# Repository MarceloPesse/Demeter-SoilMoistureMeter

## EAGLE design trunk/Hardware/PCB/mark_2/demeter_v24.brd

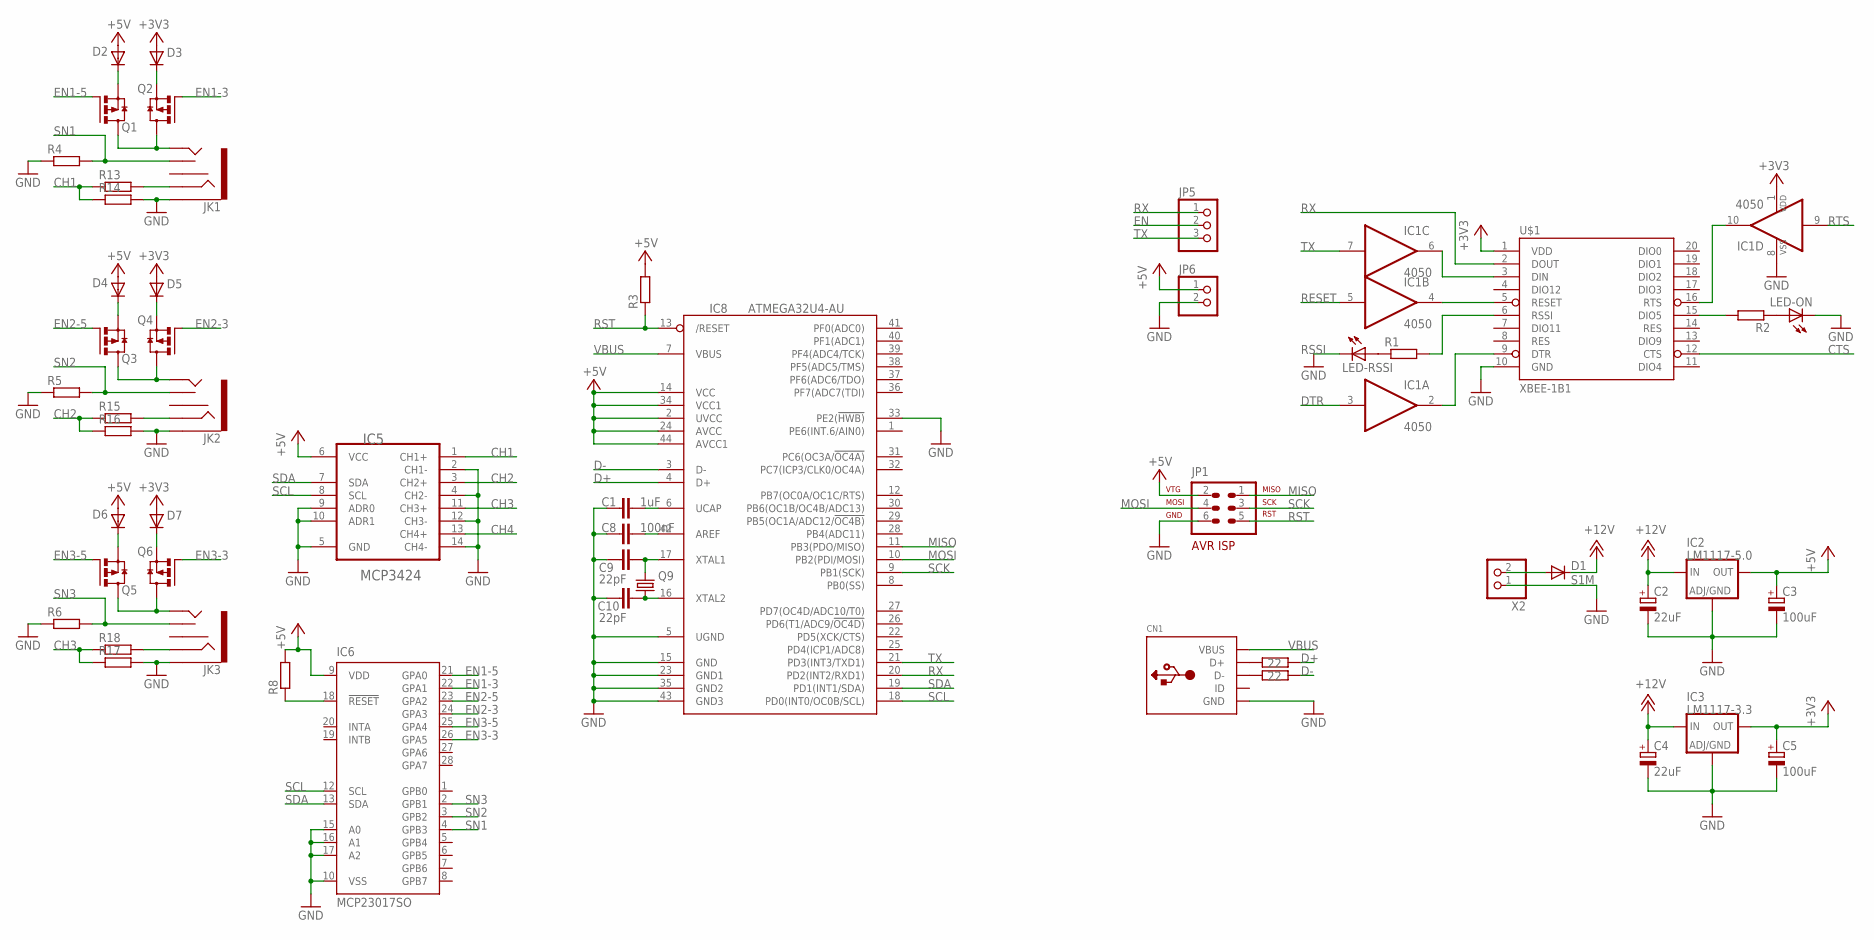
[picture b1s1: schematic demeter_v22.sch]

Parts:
C1: 1uF; C0805K
C2, C4: 22uF; PANASONIC_D
C3, C5: 100uF; PANASONIC_D
C8: 100nF; C0805K
C9, C10: 22pF; C0805K
CN1: USBMINIB; USB-MINIB
D1: S1M; DO-214AC
D2, D3, D4, D5, D6, D7: MBR0520; SOD123
IC1: 4050; SO16
IC2: LM1117-5.0; DPACK
IC3: LM1117-3.3; DPACK
IC5: MCP3424; SO14
IC6: MCP23017SO; SO28W
IC8: ATMEGA32U4-AU; TQFP44
JK1, JK2, JK3: AUDIO-JACK2PTH; AUDIO-JACK
JP1: AVR-ISP-6
JP5: PINHD-1X3180; 1X03
JP6: PINHD-1X2; 1X02
LED-ON: LED0805; CHIP-LED0805
LED-RSSI: LED0805; CHIP-LED0805
Q1, Q2, Q3, Q4, Q5, Q6: IRLML6402; SOT23
Q9: CRYSTALHC49UP; HC49UP
R1, R2, R3, R4, R5, R6, R8, R13, R14, R15, R16, R17, R18: R-EU_R0805; R0805
R9, R10: 22; R0805
U$1: XBEE-1B1; XBEE-1
X2: W237-102

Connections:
+3V3: C5.+, D3.A, D5.A, D7.A, IC1.1 (VDD), IC3.4 (OUT), U$1.1 (VDD); also elsewhere on the board
+5V: C3.+, D2.A, D4.A, D6.A, IC2.4 (OUT), IC5.6 (VCC), IC6.9 (VDD), IC8.2 (UVCC), IC8.14 (VCC), IC8.24 (AVCC), IC8.34 (VCC1), IC8.44 (AVCC1), JP1.2 (VTG), JP6.1, R3.2, R8.2; also elsewhere on the board
+12V: C2.+, C4.+, D1.C, IC2.3 (IN), IC3.3 (IN)
CH1: IC5.1 (CH1+), R13.1, R14.1
CH2: IC5.3 (CH2+), R15.1, R16.1
CH3: IC5.11 (CH3+), R17.1, R18.1
CTS: U$1.12 (CTS); also elsewhere on the board
D+: IC8.4 (D+), R9.1
D-: IC8.3 (D-), R10.1
DTR: IC1.3 (I); also elsewhere on the board
EN: JP5.2; also elsewhere on the board
EN1-3: IC6.22 (GPA1), Q2.1 (G)
EN1-5: IC6.21 (GPA0), Q1.1 (G)
EN2-3: IC6.24 (GPA3), Q4.1 (G)
EN2-5: IC6.23 (GPA2), Q3.1 (G)
EN3-3: IC6.26 (GPA5), Q6.1 (G)
EN3-5: IC6.25 (GPA4), Q5.1 (G)
MISO: IC8.11 (PB3(PDO/MISO)), JP1.1 (MISO)
MOSI: IC8.10 (PB2(PDI/MOSI)), JP1.4 (MOSI)
unnamed: IC1.6 (O), U$1.3 (DIN)
unnamed: IC1.4 (O), U$1.5 (RESET)
unnamed 24: LED-RSSI.A, R1.1; also elsewhere on the board
unnamed: IC1.2 (O), U$1.9 (DTR)
unnamed: IC1.10 (O), U$1.16 (RTS)
unnamed: IC6.18 (!RESET), R8.1
unnamed: JK1.TIP, Q1.3 (D), Q2.3 (D)
unnamed: D2.C, Q1.2 (S)
unnamed: D3.C, Q2.2 (S)
unnamed: JK2.TIP, Q3.3 (D), Q4.3 (D)
unnamed: D4.C, Q3.2 (S)
unnamed: D5.C, Q4.2 (S)
unnamed: JK3.TIP, Q5.3 (D), Q6.3 (D)
unnamed: D6.C, Q5.2 (S)
unnamed: D7.C, Q6.2 (S)
unnamed: C1.1, IC8.6 (UCAP)
unnamed: C8.1, IC8.42 (AREF)
unnamed: C9.1, IC8.17 (XTAL1), Q9.2
unnamed: C10.1, IC8.16 (XTAL2), Q9.1
unnamed: CN1.D+, R9.2
unnamed: CN1.D-, R10.2
unnamed: JK1.RING, R13.2
unnamed: JK2.RING, R15.2
unnamed: JK3.RING, R18.2
unnamed: LED-ON.A, R2.1
unnamed: R2.2, U$1.15 (DIO5)
RESET: IC1.5 (I); also elsewhere on the board
RSSI: R1.2, U$1.6 (RSSI)
RST: IC8.13 (/RESET), JP1.5 (RST), R3.1
RTS: IC1.9 (I); also elsewhere on the board
RX: IC8.20 (PD2(INT2/RXD1)), JP5.1, U$1.2 (DOUT); also elsewhere on the board
SCK: IC8.9 (PB1(SCK)), JP1.3 (SCK)
SCL: IC5.8 (SCL), IC6.12 (SCL), IC8.18 (PD0(INT0/OC0B/SCL))
SDA: IC5.7 (SDA), IC6.13 (SDA), IC8.19 (PD1(INT1/SDA))
TX: IC1.7 (I), IC8.21 (PD3(INT3/TXD1)), JP5.3; also elsewhere on the board
VBUS: CN1.VBUS, IC8.7 (VBUS)

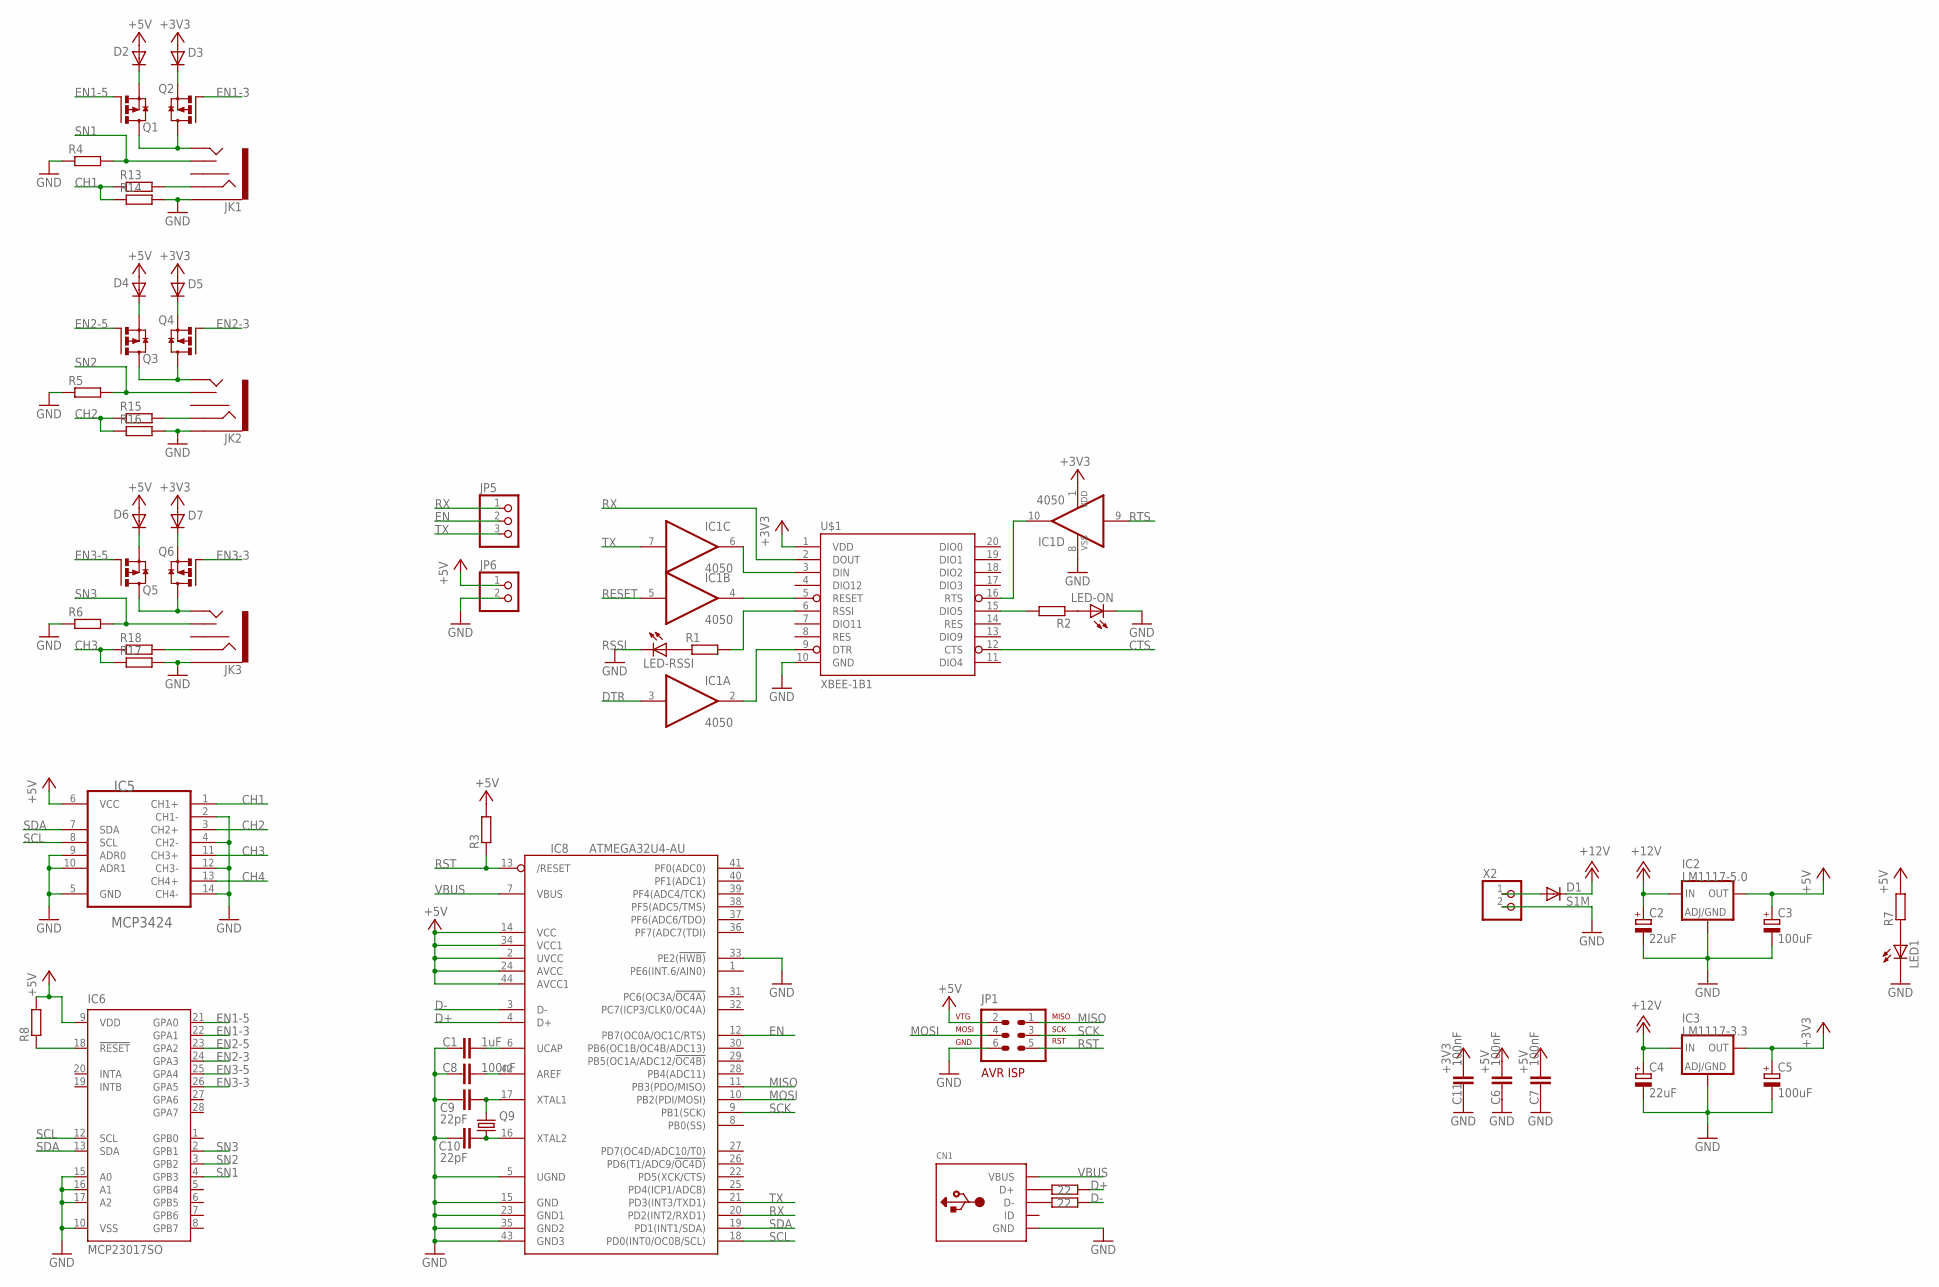
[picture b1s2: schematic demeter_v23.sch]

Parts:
C1: 1uF; C0805K
C2, C4: 22uF; PANASONIC_D
C3, C5: 100uF; PANASONIC_D
C6, C7, C8, C11: 100nF; C0805K
C9, C10: 22pF; C0805K
CN1: USBMINIB; USB-MINIB
D1: S1M; DO-214AC
D2, D3, D4, D5, D6, D7: MBR0520; SOD123
IC1: 4050; SO16
IC2: LM1117-5.0; DPACK
IC3: LM1117-3.3; DPACK
IC5: MCP3424; SO14
IC6: MCP23017SO; SO28W
IC8: ATMEGA32U4-AU; TQFP44
JK1, JK2, JK3: AUDIO-JACK2PTH; AUDIO-JACK
JP1: AVR-ISP-6
JP5: PINHD-1X3180; 1X03
JP6: PINHD-1X2; 1X02
LED1: LED0805; CHIP-LED0805
LED-ON: LED0805; CHIP-LED0805
LED-RSSI: LED0805; CHIP-LED0805
Q1, Q2, Q3, Q4, Q5, Q6: IRLML6402; SOT23
Q9: CRYSTALHC49UP; HC49UP
R1, R2, R3, R4, R5, R6, R7, R8, R13, R14, R15, R16, R17, R18: R-EU_R0805; R0805
R9, R10: 22; R0805
U$1: XBEE-1B1; XBEE-1
X2: W237-102

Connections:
+3V3: C5.+, C11.1, D3.A, D5.A, D7.A, IC1.1 (VDD), IC3.4 (OUT), U$1.1 (VDD); also elsewhere on the board
+5V: C3.+, C6.1, C7.1, D2.A, D4.A, D6.A, IC2.4 (OUT), IC5.6 (VCC), IC6.9 (VDD), IC8.2 (UVCC), IC8.14 (VCC), IC8.24 (AVCC), IC8.34 (VCC1), IC8.44 (AVCC1), JP1.2 (VTG), JP6.1, R3.2, R7.2, R8.2; also elsewhere on the board
+12V: C2.+, C4.+, D1.C, IC2.3 (IN), IC3.3 (IN)
CH1: IC5.1 (CH1+), R13.1, R14.1
CH2: IC5.3 (CH2+), R15.1, R16.1
CH3: IC5.11 (CH3+), R17.1, R18.1
CTS: U$1.12 (CTS); also elsewhere on the board
D+: IC8.4 (D+), R9.1
D-: IC8.3 (D-), R10.1
DTR: IC1.3 (I); also elsewhere on the board
EN: IC8.12 (PB7(OC0A/OC1C/RTS)), JP5.2
EN1-3: IC6.22 (GPA1), Q2.1 (G)
EN1-5: IC6.21 (GPA0), Q1.1 (G)
EN2-3: IC6.24 (GPA3), Q4.1 (G)
EN2-5: IC6.23 (GPA2), Q3.1 (G)
EN3-3: IC6.26 (GPA5), Q6.1 (G)
EN3-5: IC6.25 (GPA4), Q5.1 (G)
MISO: IC8.11 (PB3(PDO/MISO)), JP1.1 (MISO)
MOSI: IC8.10 (PB2(PDI/MOSI)), JP1.4 (MOSI)
unnamed 20: LED1.A, R7.1; also elsewhere on the board
unnamed: IC1.6 (O), U$1.3 (DIN)
unnamed: IC1.4 (O), U$1.5 (RESET)
unnamed 24: LED-RSSI.A, R1.1; also elsewhere on the board
unnamed: IC1.2 (O), U$1.9 (DTR)
unnamed: IC1.10 (O), U$1.16 (RTS)
unnamed: IC6.18 (!RESET), R8.1
unnamed: JK1.TIP, Q1.3 (D), Q2.3 (D)
unnamed: D2.C, Q1.2 (S)
unnamed: D3.C, Q2.2 (S)
unnamed: JK2.TIP, Q3.3 (D), Q4.3 (D)
unnamed: D4.C, Q3.2 (S)
unnamed: D5.C, Q4.2 (S)
unnamed: JK3.TIP, Q5.3 (D), Q6.3 (D)
unnamed: D6.C, Q5.2 (S)
unnamed: D7.C, Q6.2 (S)
unnamed: C1.1, IC8.6 (UCAP)
unnamed: C8.1, IC8.42 (AREF)
unnamed: C9.1, IC8.17 (XTAL1), Q9.2
unnamed: C10.1, IC8.16 (XTAL2), Q9.1
unnamed: CN1.D+, R9.2
unnamed: CN1.D-, R10.2
unnamed: JK1.RING, R13.2
unnamed: JK2.RING, R15.2
unnamed: JK3.RING, R18.2
unnamed: LED-ON.A, R2.1
unnamed: R2.2, U$1.15 (DIO5)
RESET: IC1.5 (I); also elsewhere on the board
RSSI: R1.2, U$1.6 (RSSI)
RST: IC8.13 (/RESET), JP1.5 (RST), R3.1
RTS: IC1.9 (I); also elsewhere on the board
RX: IC8.20 (PD2(INT2/RXD1)), JP5.1, U$1.2 (DOUT); also elsewhere on the board
SCK: IC8.9 (PB1(SCK)), JP1.3 (SCK)
SCL: IC5.8 (SCL), IC6.12 (SCL), IC8.18 (PD0(INT0/OC0B/SCL))
SDA: IC5.7 (SDA), IC6.13 (SDA), IC8.19 (PD1(INT1/SDA))
TX: IC1.7 (I), IC8.21 (PD3(INT3/TXD1)), JP5.3; also elsewhere on the board
VBUS: CN1.VBUS, IC8.7 (VBUS)

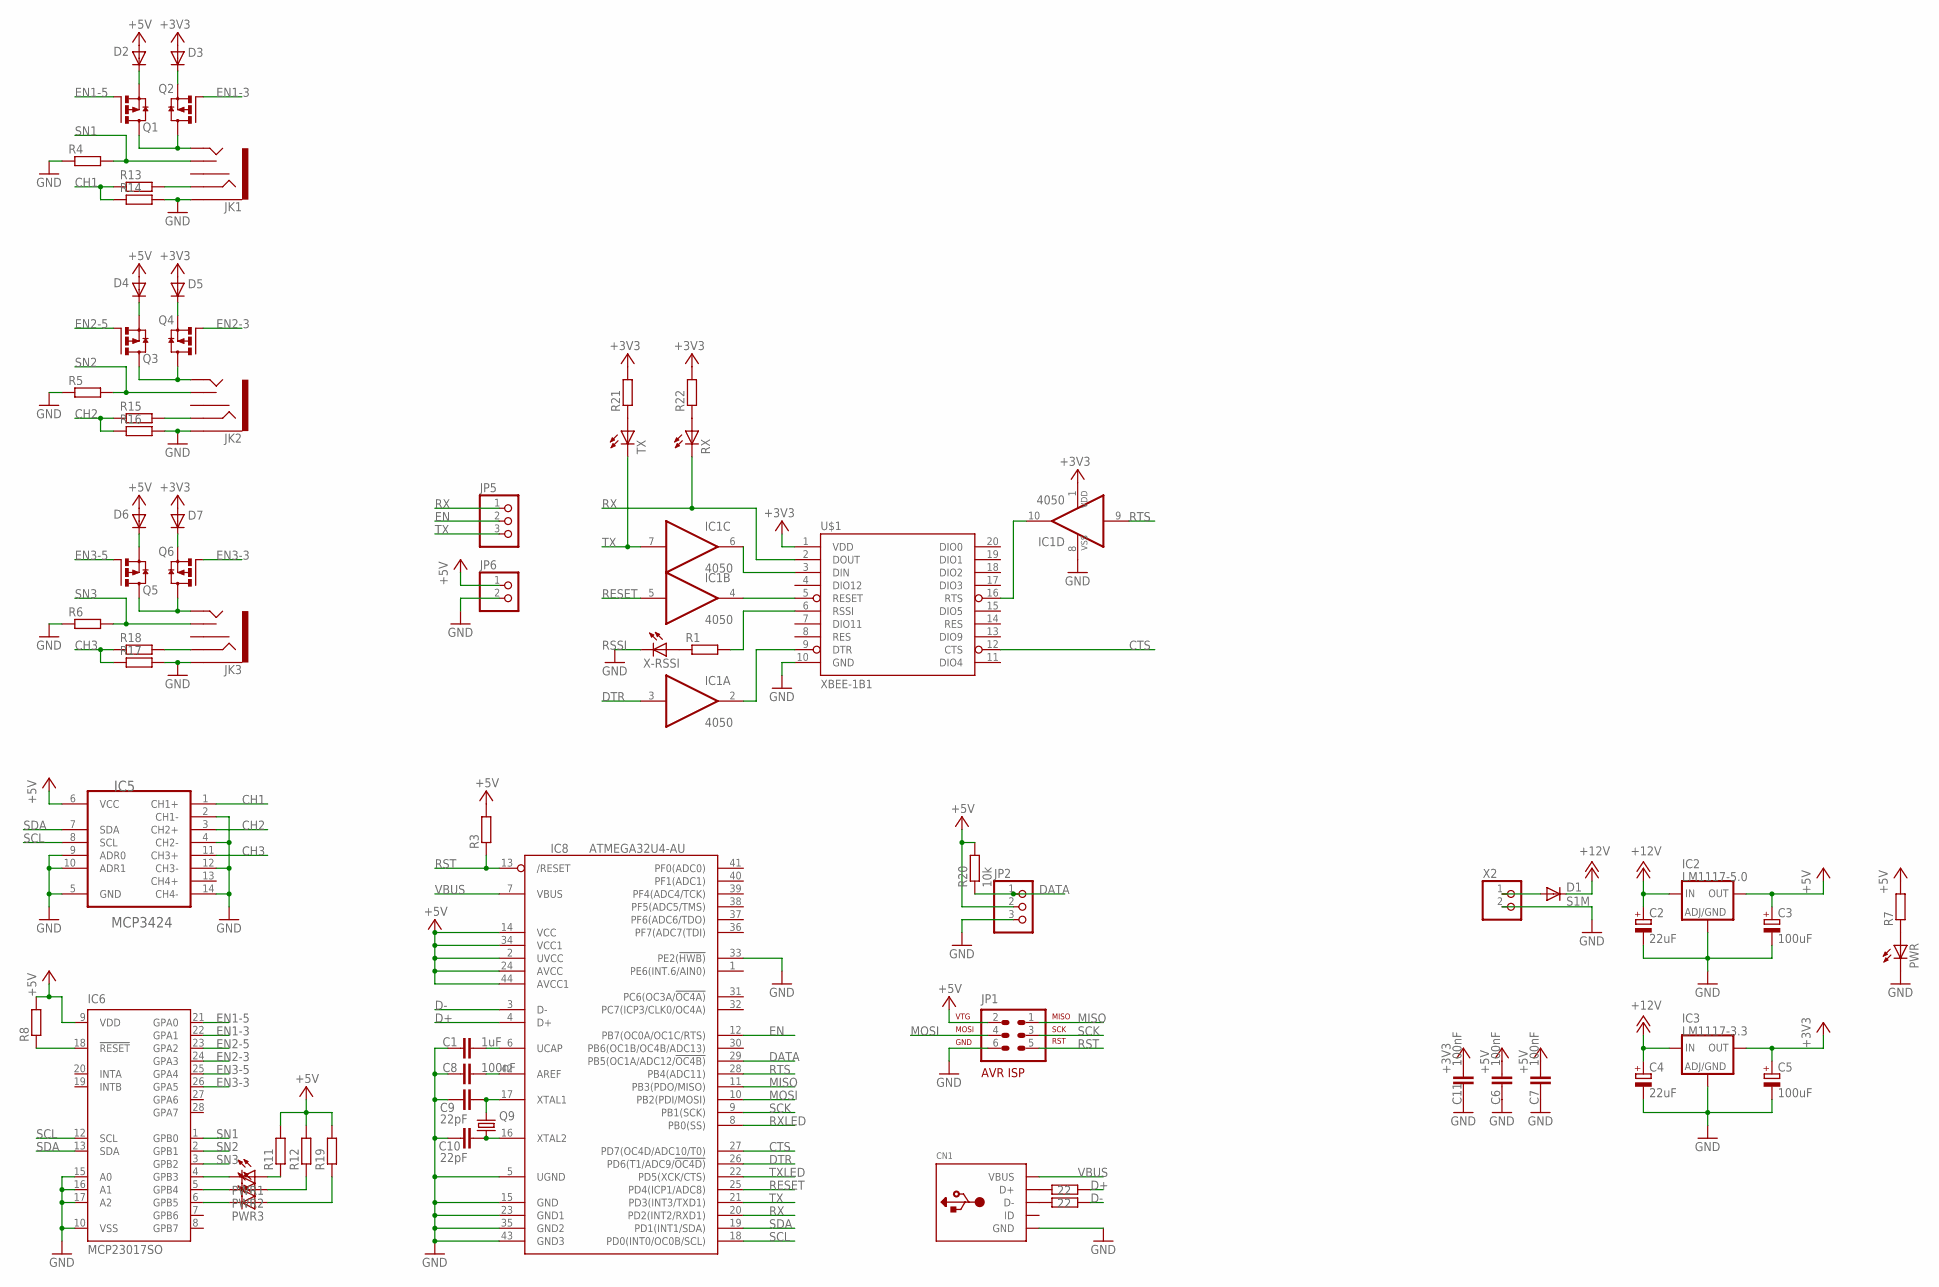
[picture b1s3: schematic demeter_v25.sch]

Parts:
C1: 1uF; C0805K
C2, C4: 22uF; PANASONIC_D
C3, C5: 100uF; PANASONIC_D
C6, C7, C8, C11: 100nF; C0805K
C9, C10: 22pF; C0805K
CN1: USBMINIB; USB-MINIB
D1: S1M; DO-214AC
D2, D3, D4, D5, D6, D7: MBR0520; SOD123
IC1: 4050; SO16
IC2: LM1117-5.0; DPACK
IC3: LM1117-3.3; DPACK
IC5: MCP3424; SO14
IC6: MCP23017SO; SO28W
IC8: ATMEGA32U4-AU; TQFP44
JK1, JK2, JK3: AUDIO-JACK2PTH; AUDIO-JACK
JP1: AVR-ISP-6
JP2, JP5: PINHD-1X3180; 1X03
JP6: PINHD-1X2; 1X02
PWR, PWR1, PWR2, PWR3: LED0805; CHIP-LED0805
Q1, Q2, Q3, Q4, Q5, Q6: IRLML6402; SOT23
Q9: CRYSTALHC49UP; HC49UP
R1, R3, R4, R5, R6, R7, R8, R11, R12, R13, R14, R15, R16, R17, R18, R19, R21, R22: R-EU_R0805; R0805
R9, R10: 22; R0805
R20: 10k; R0805
RX: LED0805; CHIP-LED0805
TX: LED0805; CHIP-LED0805
U$1: XBEE-1B1; XBEE-1
X2: W237-102
X-RSSI: LED0805; CHIP-LED0805

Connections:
+3V3: C5.+, C11.1, D3.A, D5.A, D7.A, IC1.1 (VDD), IC3.4 (OUT), R21.2, R22.2, U$1.1 (VDD)
+5V: C3.+, C6.1, C7.1, D2.A, D4.A, D6.A, IC2.4 (OUT), IC5.6 (VCC), IC6.9 (VDD), IC8.2 (UVCC), IC8.14 (VCC), IC8.24 (AVCC), IC8.34 (VCC1), IC8.44 (AVCC1), JP1.2 (VTG), JP2.2, JP6.1, R3.2, R7.2, R8.2, R11.2, R12.2, R19.2, R20.2
+12V: C2.+, C4.+, D1.C, IC2.3 (IN), IC3.3 (IN)
CH1: IC5.1 (CH1+), R13.1, R14.1
CH2: IC5.3 (CH2+), R15.1, R16.1
CH3: IC5.11 (CH3+), R17.1, R18.1
CTS: IC8.27 (PD7(OC4D/ADC10/T0)), U$1.12 (CTS)
D+: IC8.4 (D+), R9.1
D-: IC8.3 (D-), R10.1
DATA: IC8.29 (PB5(OC1A/ADC12/!OC4B)), JP2.1, R20.1
DTR: IC1.3 (I), IC8.26 (PD6(T1/ADC9/!OC4D))
EN: IC8.12 (PB7(OC0A/OC1C/RTS)), JP5.2
EN1-3: IC6.22 (GPA1), Q2.1 (G)
EN1-5: IC6.21 (GPA0), Q1.1 (G)
EN2-3: IC6.24 (GPA3), Q4.1 (G)
EN2-5: IC6.23 (GPA2), Q3.1 (G)
EN3-3: IC6.26 (GPA5), Q6.1 (G)
EN3-5: IC6.25 (GPA4), Q5.1 (G)
MISO: IC8.11 (PB3(PDO/MISO)), JP1.1 (MISO)
MOSI: IC8.10 (PB2(PDI/MOSI)), JP1.4 (MOSI)
unnamed 20: PWR.A, R7.1; also elsewhere on the board
unnamed: IC1.6 (O), U$1.3 (DIN)
unnamed: IC1.4 (O), U$1.5 (RESET)
unnamed: PWR1.A, R11.1
unnamed 24: R1.1, X-RSSI.A; also elsewhere on the board
unnamed: IC1.2 (O), U$1.9 (DTR)
unnamed: IC1.10 (O), U$1.16 (RTS)
unnamed: IC6.18 (!RESET), R8.1
unnamed: JK1.TIP, Q1.3 (D), Q2.3 (D)
unnamed: D2.C, Q1.2 (S)
unnamed: D3.C, Q2.2 (S)
unnamed: JK2.TIP, Q3.3 (D), Q4.3 (D)
unnamed: D4.C, Q3.2 (S)
unnamed: D5.C, Q4.2 (S)
unnamed: JK3.TIP, Q5.3 (D), Q6.3 (D)
unnamed: D6.C, Q5.2 (S)
unnamed: D7.C, Q6.2 (S)
unnamed: PWR2.A, R12.1
unnamed: PWR3.A, R19.1
unnamed: C1.1, IC8.6 (UCAP)
unnamed: C8.1, IC8.42 (AREF)
unnamed: C9.1, IC8.17 (XTAL1), Q9.2
unnamed: C10.1, IC8.16 (XTAL2), Q9.1
unnamed: CN1.D+, R9.2
unnamed: CN1.D-, R10.2
unnamed: JK1.RING, R13.2
unnamed: JK2.RING, R15.2
unnamed: IC6.5 (GPB4), PWR2.C
unnamed: JK3.RING, R18.2
unnamed: R21.1, TX.A
unnamed: R22.1, RX.A
RESET: IC1.5 (I), IC8.25 (PD4(ICP1/ADC8))
RSSI: R1.2, U$1.6 (RSSI)
RST: IC8.13 (/RESET), JP1.5 (RST), R3.1
RTS: IC1.9 (I), IC8.28 (PB4(ADC11))
RX: IC8.20 (PD2(INT2/RXD1)), JP5.1, RX.C, U$1.2 (DOUT)
RXLED: IC8.8 (PB0(SS))
SCK: IC8.9 (PB1(SCK)), JP1.3 (SCK)
SCL: IC5.8 (SCL), IC6.12 (SCL), IC8.18 (PD0(INT0/OC0B/SCL))
SDA: IC5.7 (SDA), IC6.13 (SDA), IC8.19 (PD1(INT1/SDA))
TX: IC1.7 (I), IC8.21 (PD3(INT3/TXD1)), JP5.3, TX.C
TXLED: IC8.22 (PD5(XCK/CTS))
VBUS: CN1.VBUS, IC8.7 (VBUS)

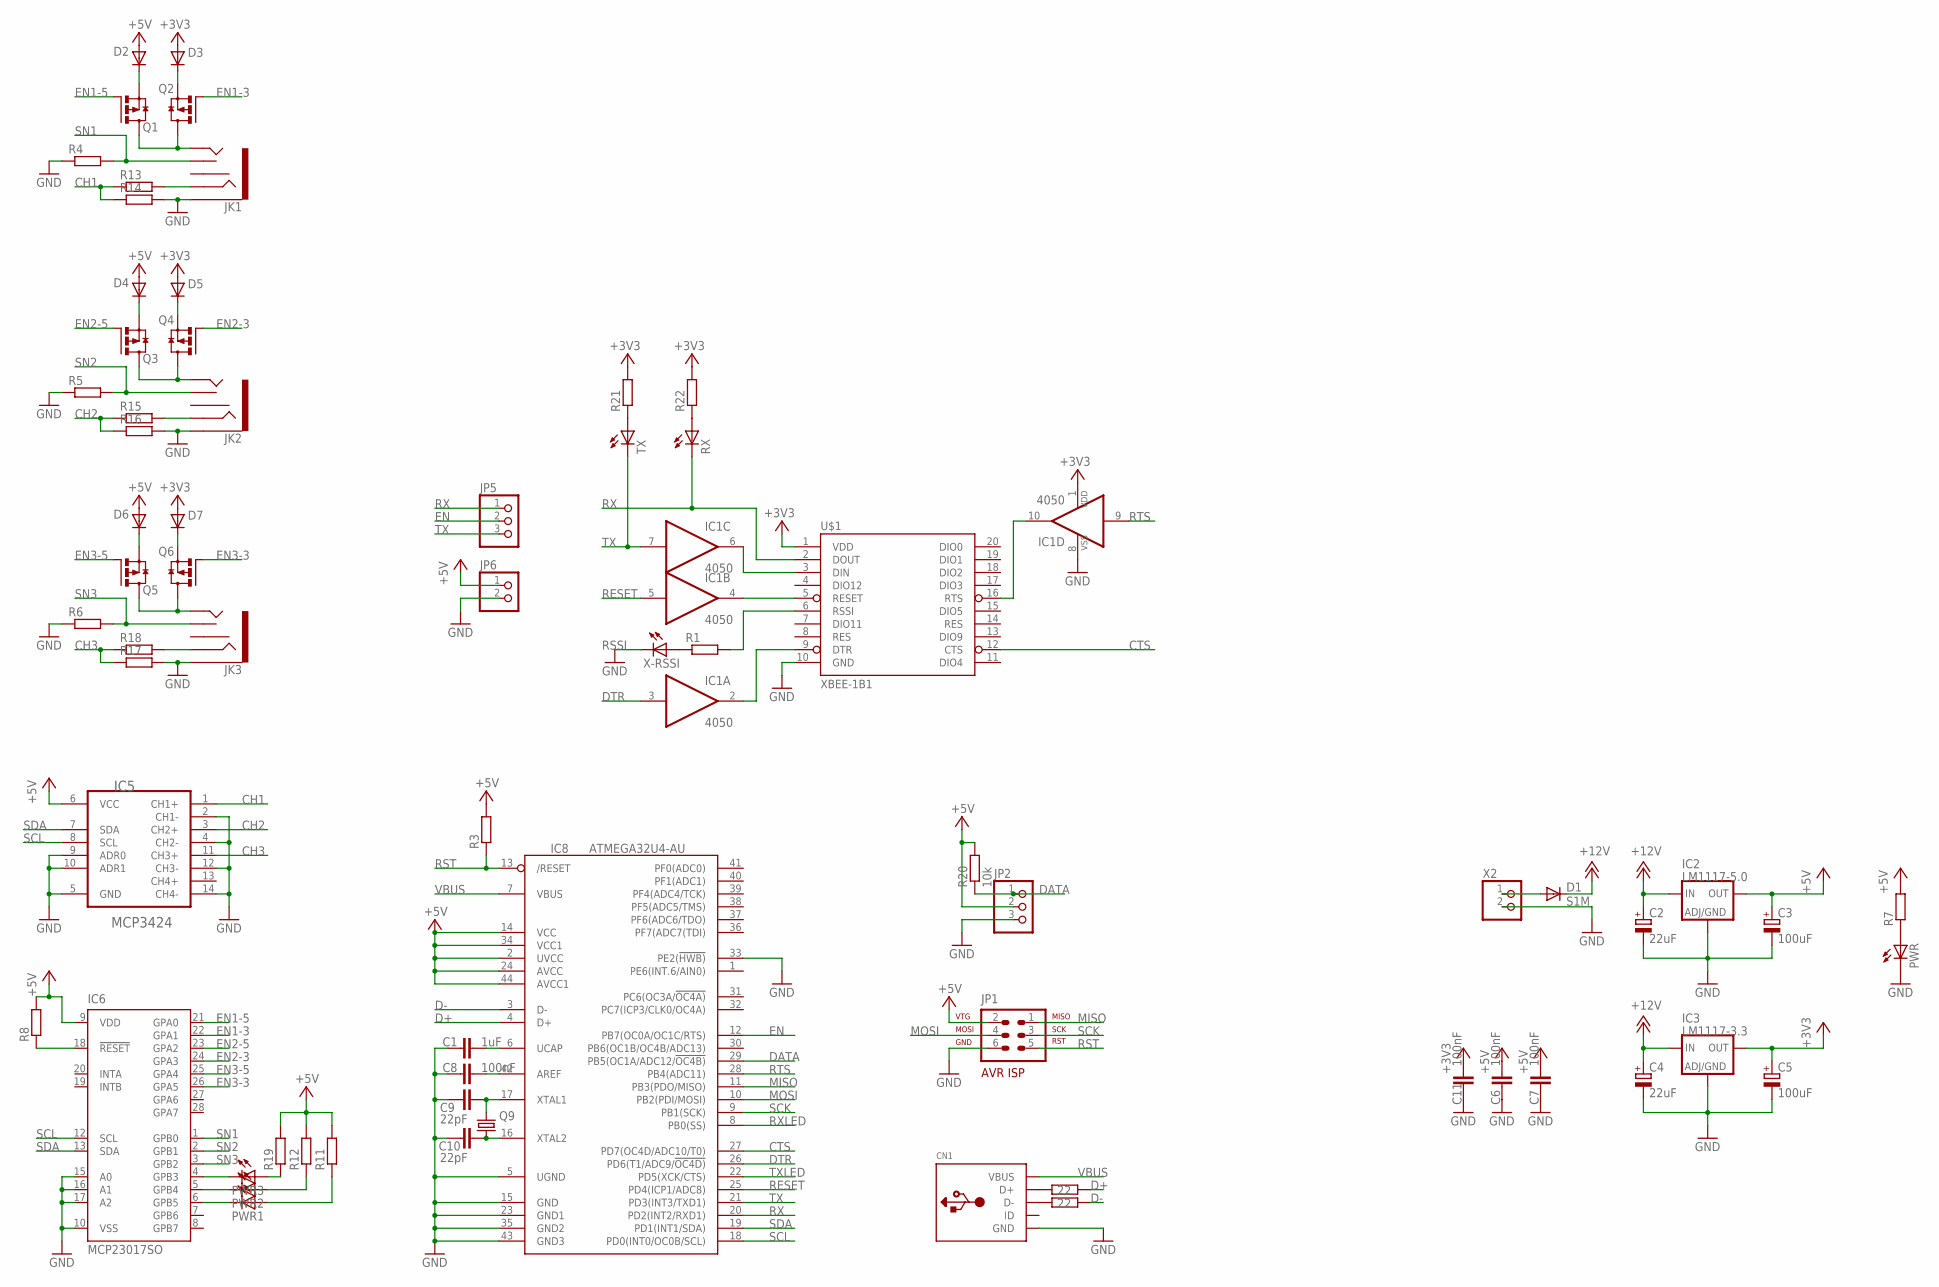
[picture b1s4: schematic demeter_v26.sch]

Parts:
C1: 1uF; C0805K
C2, C4: 22uF; PANASONIC_D
C3, C5: 100uF; PANASONIC_D
C6, C7, C8, C11: 100nF; C0805K
C9, C10: 22pF; C0805K
CN1: USBMINIB; USB-MINIB
D1: S1M; DO-214AC
D2, D3, D4, D5, D6, D7: MBR0520; SOD123
IC1: 4050; SO16
IC2: LM1117-5.0; DPACK
IC3: LM1117-3.3; DPACK
IC5: MCP3424; SO14
IC6: MCP23017SO; SO28W
IC8: ATMEGA32U4-AU; TQFP44
JK1, JK2, JK3: AUDIO-JACK2PTH; AUDIO-JACK
JP1: AVR-ISP-6
JP2, JP5: PINHD-1X3180; 1X03
JP6: PINHD-1X2; 1X02
PWR, PWR1, PWR2, PWR3: LED0805; CHIP-LED0805
Q1, Q2, Q3, Q4, Q5, Q6: IRLML6402; SOT23
Q9: CRYSTALHC49UP; HC49UP
R1, R3, R4, R5, R6, R7, R8, R11, R12, R13, R14, R15, R16, R17, R18, R19, R21, R22: R-EU_R0805; R0805
R9, R10: 22; R0805
R20: 10k; R0805
RX: LED0805; CHIP-LED0805
TX: LED0805; CHIP-LED0805
U$1: XBEE-1B1; XBEE-1
X2: W237-102
X-RSSI: LED0805; CHIP-LED0805

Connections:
+3V3: C5.+, C11.1, D3.A, D5.A, D7.A, IC1.1 (VDD), IC3.4 (OUT), R21.2, R22.2, U$1.1 (VDD)
+5V: C3.+, C6.1, C7.1, D2.A, D4.A, D6.A, IC2.4 (OUT), IC5.6 (VCC), IC6.9 (VDD), IC8.2 (UVCC), IC8.14 (VCC), IC8.24 (AVCC), IC8.34 (VCC1), IC8.44 (AVCC1), JP1.2 (VTG), JP2.2, JP6.1, R3.2, R7.2, R8.2, R11.2, R12.2, R19.2, R20.2
+12V: C2.+, C4.+, D1.C, IC2.3 (IN), IC3.3 (IN)
CH1: IC5.1 (CH1+), R13.1, R14.1
CH2: IC5.3 (CH2+), R15.1, R16.1
CH3: IC5.11 (CH3+), R17.1, R18.1
CTS: IC8.27 (PD7(OC4D/ADC10/T0)), U$1.12 (CTS)
D+: IC8.4 (D+), R9.1
D-: IC8.3 (D-), R10.1
DATA: IC8.29 (PB5(OC1A/ADC12/!OC4B)), JP2.1, R20.1
DTR: IC1.3 (I), IC8.26 (PD6(T1/ADC9/!OC4D))
EN: IC8.12 (PB7(OC0A/OC1C/RTS)), JP5.2
EN1-3: IC6.22 (GPA1), Q2.1 (G)
EN1-5: IC6.21 (GPA0), Q1.1 (G)
EN2-3: IC6.24 (GPA3), Q4.1 (G)
EN2-5: IC6.23 (GPA2), Q3.1 (G)
EN3-3: IC6.26 (GPA5), Q6.1 (G)
EN3-5: IC6.25 (GPA4), Q5.1 (G)
MISO: IC8.11 (PB3(PDO/MISO)), JP1.1 (MISO)
MOSI: IC8.10 (PB2(PDI/MOSI)), JP1.4 (MOSI)
unnamed 20: PWR.A, R7.1; also elsewhere on the board
unnamed: IC1.6 (O), U$1.3 (DIN)
unnamed: IC1.4 (O), U$1.5 (RESET)
unnamed: PWR1.A, R11.1
unnamed 24: R1.1, X-RSSI.A; also elsewhere on the board
unnamed: IC1.2 (O), U$1.9 (DTR)
unnamed: IC1.10 (O), U$1.16 (RTS)
unnamed: IC6.18 (!RESET), R8.1
unnamed: JK1.TIP, Q1.3 (D), Q2.3 (D)
unnamed: D2.C, Q1.2 (S)
unnamed: D3.C, Q2.2 (S)
unnamed: JK2.TIP, Q3.3 (D), Q4.3 (D)
unnamed: D4.C, Q3.2 (S)
unnamed: D5.C, Q4.2 (S)
unnamed: JK3.TIP, Q5.3 (D), Q6.3 (D)
unnamed: D6.C, Q5.2 (S)
unnamed: D7.C, Q6.2 (S)
unnamed: PWR2.A, R12.1
unnamed: PWR3.A, R19.1
unnamed: C1.1, IC8.6 (UCAP)
unnamed: C8.1, IC8.42 (AREF)
unnamed: C9.1, IC8.17 (XTAL1), Q9.2
unnamed: C10.1, IC8.16 (XTAL2), Q9.1
unnamed: CN1.D+, R9.2
unnamed: CN1.D-, R10.2
unnamed: JK1.RING, R13.2
unnamed: JK2.RING, R15.2
unnamed: IC6.5 (GPB4), PWR2.C
unnamed: JK3.RING, R18.2
unnamed: R21.1, TX.A
unnamed: R22.1, RX.A
RESET: IC1.5 (I), IC8.25 (PD4(ICP1/ADC8))
RSSI: R1.2, U$1.6 (RSSI)
RST: IC8.13 (/RESET), JP1.5 (RST), R3.1
RTS: IC1.9 (I), IC8.28 (PB4(ADC11))
RX: IC8.20 (PD2(INT2/RXD1)), JP5.1, RX.C, U$1.2 (DOUT)
RXLED: IC8.8 (PB0(SS))
SCK: IC8.9 (PB1(SCK)), JP1.3 (SCK)
SCL: IC5.8 (SCL), IC6.12 (SCL), IC8.18 (PD0(INT0/OC0B/SCL))
SDA: IC5.7 (SDA), IC6.13 (SDA), IC8.19 (PD1(INT1/SDA))
TX: IC1.7 (I), IC8.21 (PD3(INT3/TXD1)), JP5.3, TX.C
TXLED: IC8.22 (PD5(XCK/CTS))
VBUS: CN1.VBUS, IC8.7 (VBUS)

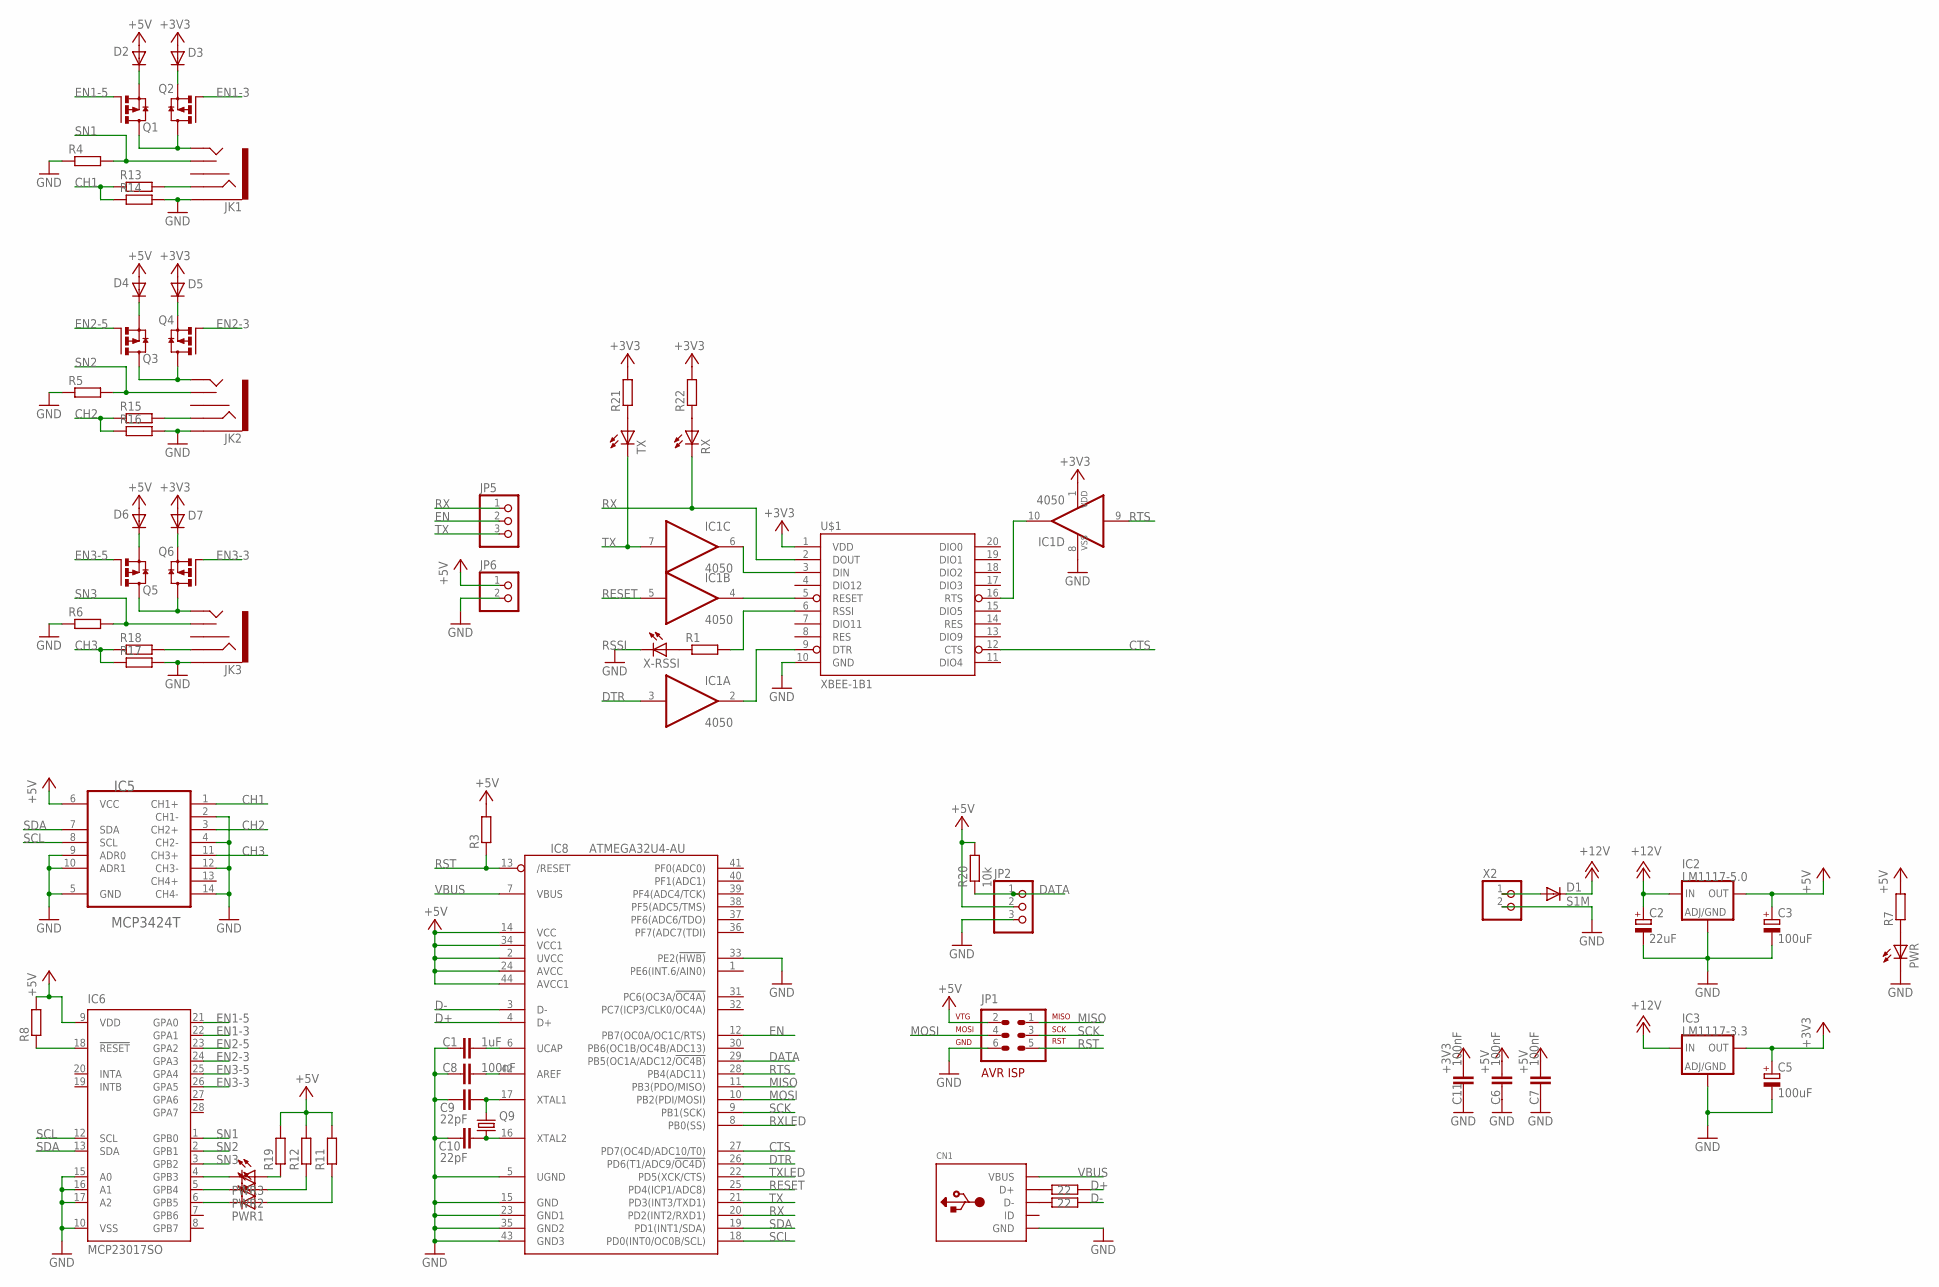
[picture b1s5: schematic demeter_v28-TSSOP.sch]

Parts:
C1: 1uF; C0805K
C2: 22uF; PANASONIC_D
C3, C5: 100uF; PANASONIC_D
C6, C7, C8, C11: 100nF; C0805K
C9, C10: 22pF; C0805K
CN1: USBMINIB; USB-MINIB
D1: S1M; DO-214AC
D2, D3, D4, D5, D6, D7: MBR0520; SOD123
IC1: 4050; SO16
IC2: LM1117-5.0; DPACK
IC3: LM1117-3.3; DPACK
IC5: MCP3424T; TSSOP14
IC6: MCP23017SO; SO28W
IC8: ATMEGA32U4-AU; TQFP44
JK1, JK2, JK3: AUDIO-JACK2PTH; AUDIO-JACK
JP1: AVR-ISP-6
JP2, JP5: PINHD-1X3180; 1X03
JP6: PINHD-1X2; 1X02
PWR, PWR1, PWR2, PWR3: LED0805; CHIP-LED0805
Q1, Q2, Q3, Q4, Q5, Q6: IRLML6402; SOT23
Q9: CRYSTALHC49UP; HC49UP
R1, R3, R4, R5, R6, R7, R8, R11, R12, R13, R14, R15, R16, R17, R18, R19, R21, R22: R-EU_R0805; R0805
R9, R10: 22; R0805
R20: 10k; R0805
RX: LED0805; CHIP-LED0805
TX: LED0805; CHIP-LED0805
U$1: XBEE-1B1; XBEE-1
X2: W237-102
X-RSSI: LED0805; CHIP-LED0805

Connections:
+3V3: C5.+, C11.1, D3.A, D5.A, D7.A, IC1.1 (VDD), IC3.4 (OUT), R21.2, R22.2, U$1.1 (VDD)
+5V: C3.+, C6.1, C7.1, D2.A, D4.A, D6.A, IC2.4 (OUT), IC5.6 (VCC), IC6.9 (VDD), IC8.2 (UVCC), IC8.14 (VCC), IC8.24 (AVCC), IC8.34 (VCC1), IC8.44 (AVCC1), JP1.2 (VTG), JP2.2, JP6.1, R3.2, R7.2, R8.2, R11.2, R12.2, R19.2, R20.2
+12V: C2.+, D1.C, IC2.3 (IN), IC3.3 (IN); also elsewhere on the board
CH1: IC5.1 (CH1+), R13.1, R14.1
CH2: IC5.3 (CH2+), R15.1, R16.1
CH3: IC5.11 (CH3+), R17.1, R18.1
CTS: IC8.27 (PD7(OC4D/ADC10/T0)), U$1.12 (CTS)
D+: IC8.4 (D+), R9.1
D-: IC8.3 (D-), R10.1
DATA: IC8.29 (PB5(OC1A/ADC12/!OC4B)), JP2.1, R20.1
DTR: IC1.3 (I), IC8.26 (PD6(T1/ADC9/!OC4D))
EN: IC8.12 (PB7(OC0A/OC1C/RTS)), JP5.2
EN1-3: IC6.22 (GPA1), Q2.1 (G)
EN1-5: IC6.21 (GPA0), Q1.1 (G)
EN2-3: IC6.24 (GPA3), Q4.1 (G)
EN2-5: IC6.23 (GPA2), Q3.1 (G)
EN3-3: IC6.26 (GPA5), Q6.1 (G)
EN3-5: IC6.25 (GPA4), Q5.1 (G)
MISO: IC8.11 (PB3(PDO/MISO)), JP1.1 (MISO)
MOSI: IC8.10 (PB2(PDI/MOSI)), JP1.4 (MOSI)
unnamed 20: PWR.A, R7.1; also elsewhere on the board
unnamed: IC1.6 (O), U$1.3 (DIN)
unnamed: IC1.4 (O), U$1.5 (RESET)
unnamed: PWR1.A, R11.1
unnamed 24: R1.1, X-RSSI.A; also elsewhere on the board
unnamed: IC1.2 (O), U$1.9 (DTR)
unnamed: IC1.10 (O), U$1.16 (RTS)
unnamed: IC6.18 (!RESET), R8.1
unnamed: JK1.TIP, Q1.3 (D), Q2.3 (D)
unnamed: D2.C, Q1.2 (S)
unnamed: D3.C, Q2.2 (S)
unnamed: JK2.TIP, Q3.3 (D), Q4.3 (D)
unnamed: D4.C, Q3.2 (S)
unnamed: D5.C, Q4.2 (S)
unnamed: JK3.TIP, Q5.3 (D), Q6.3 (D)
unnamed: D6.C, Q5.2 (S)
unnamed: D7.C, Q6.2 (S)
unnamed: PWR2.A, R12.1
unnamed: PWR3.A, R19.1
unnamed: C1.1, IC8.6 (UCAP)
unnamed: C8.1, IC8.42 (AREF)
unnamed: C9.1, IC8.17 (XTAL1), Q9.2
unnamed: C10.1, IC8.16 (XTAL2), Q9.1
unnamed: CN1.D+, R9.2
unnamed: CN1.D-, R10.2
unnamed: JK1.RING, R13.2
unnamed: JK2.RING, R15.2
unnamed: IC6.5 (GPB4), PWR2.C
unnamed: JK3.RING, R18.2
unnamed: R21.1, TX.A
unnamed: R22.1, RX.A
RESET: IC1.5 (I), IC8.25 (PD4(ICP1/ADC8))
RSSI: R1.2, U$1.6 (RSSI)
RST: IC8.13 (/RESET), JP1.5 (RST), R3.1
RTS: IC1.9 (I), IC8.28 (PB4(ADC11))
RX: IC8.20 (PD2(INT2/RXD1)), JP5.1, RX.C, U$1.2 (DOUT)
RXLED: IC8.8 (PB0(SS))
SCK: IC8.9 (PB1(SCK)), JP1.3 (SCK)
SCL: IC5.8 (SCL), IC6.12 (SCL), IC8.18 (PD0(INT0/OC0B/SCL))
SDA: IC5.7 (SDA), IC6.13 (SDA), IC8.19 (PD1(INT1/SDA))
TX: IC1.7 (I), IC8.21 (PD3(INT3/TXD1)), JP5.3, TX.C
TXLED: IC8.22 (PD5(XCK/CTS))
VBUS: CN1.VBUS, IC8.7 (VBUS)
